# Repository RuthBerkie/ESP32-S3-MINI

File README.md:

# ESP32_S3_MINI

The Complete End-to-End System Rationale

This is a comprehensive, sequential summary of how all 6 functional blocks connect, interact, and operate dynamically as a unified system. It is structured in the exact order that electricity and data flow through the board—from the moment the plug is plugged in a cable to the execution of software tasks.
 
                       [1. USB-C Input & ESD] ───> [2. Power Conditioning (LDO)] ───> [3. 3.3V System Rails Active]
                                                                                                 │
                          ┌──────────────────────────────────────────────────────────────────────┘
                          │
                          ▼
                      [4. ESP32-S3 Boot up Sequence] <─── [RC Delay Network (10ms Lock)]
                          │
                          ├───> [5. Environmental Telemetry Bus] ───> Reading Onboard HDC3022 Sensor & Qwiic Port
                          │
                          ├───> [6. Peripheral Interaction Arrays] ──> Driving Common-Anode RGB LED Matrix
                          │
                          └───> [7. High-Speed External Expansion] ──> Driving Industrial 10-Pin SPI/IRQ Interface

Step 1: Power Entry, Handshaking, and Frontline Protection 
The entire operational sequence begins at J1 (the USB-C port).

    1. The Power Handshake: When a modern USB-C to USB-C cable is used, the host charger inspects the configuration channel pins (CC1/CC2). Because the 5.1 kΩ pull-down resistors is placed (R7/R8) on these lines, the charger identifies the board as a safe power sink and turns on its 5V rail.
    2. First Line of Defense (ESD): As the user inserts the cable, any invisible static electricity shock from their fingers is instantly intercepted by U3 (the USBLC6-2SC6 TVS diode array), which clamps the high voltage and dumps it safely to the ground plane before it can enter the rest of the board.
    3. Overcurrent Intercept: The raw 5V power travels through F1 (the 1A Polyfuse). If a downstream component is shorted, this fuse heats up and chokes the current to protect your computer's USB port.
    4. Noise Choking: The electricity then passes through FB1 (the Ferrite Bead), which blocks high-frequency electronic ripple from the laptop's power adapter, providing clean, smooth 5V power to the next stage.
    5. Reverse Voltage Isolation: Finally, D3 (the Schottky Diode) acts as a one-way check valve, letting this clean 5V travel onward but preventing any external programmer power from leaking backward into your computer.

Step 2: Power Conditioning and Voltage Regulation(Picture 5) 
The filtered 5V power now reaches U1 (the LM1117-3.3 Linear Regulator).

    1. Bulk Smoothing: C1 (10µF) acts as an entry reservoir, absorbing any sudden voltage shifts right at the door of the regulator.
    2. Down-Step Regulation: U1 takes the 5V and steps it down to a stable +3.3V, burning off the extra 1.7V as heat. This 3.3V line is the primary power source for all computer chips on the board.
    3. Transient Buffering: C2 (10µF) acts as an output reservoir. When downstream chips suddenly pull large currents, C2 dumps its energy into the rail instantly to keep the voltage from dropping.
    4. Visual Diagnostics: The moment the 3.3V rail stabilizes, current travels through R6 to light up D2 (the Green LED), providing a visual confirmation that the board's power system is operating correctly.

Step 3: Hardware Boot, Clock Timing, and Brain Management
With 3.3V spreading across the inner power planes of the board, the U4 (ESP32-S3-MINI-1) module wakes up.

    1. The Startup Delay: To prevent the ESP32 from turning on during mid-voltage fluctuations, R9 (10kΩ) and C5 (1µF) form an RC delay network. They force the EN (Reset) pin to stay low for exactly 10 milliseconds, holding the processor core in a reset state until the 3.3V rail is entirely stable.
    2. Boot Mode Selection: As the 10ms timer expires and the EN pin pulls high, the ESP32 looks at its configuration "strapping pins":
	• Normal Operation: If SW3 (BOOT button) is sitting idle, GPIO0 is pulled high internally, and the chip boots straight into its flash memory to run your saved code.
	• Flashing Mode: If you hold SW3 down while tapping SW2 (RESET), GPIO0 drops to 0V (Ground). The chip detects this and switches into its download mode, allowing a computer connected via the J4 Programming Header to upload a new script over the ESP_TXD and ESP_RXD serial lines.
    3. Noise Stability: Local 10µF (C6) and 100nF (C7) decoupling capacitors sit right at the ESP32's power pins, acting as high-frequency filters to absorb voltage fluctuations caused by the processor's internal transistors.
    4. Boot Rule Adherence: R11 (the external 10kΩ pull-up) keeps GPIO3 locked safely at 3.3V, satisfying the Espressif datasheet note to prevent a floating state from causing unpredictable boot failures.

Step 4: Environmental Data Collection via the Telemetry Bus (Picture 7)
Once the ESP32-S3 code begins running, it initializes its internal I2C communication peripheral mapped to pins 12 and 13.

    1. Line Stabilization: R1 (4.7kΩ) and R2 (4.7kΩ) act as active pull-ups, holding the SDA (Serial Data) and SCL (Serial Clock) lines at 3.3V so they don't drift into electrical noise.
    2. Onboard Telemetry: The ESP32 acts as the master, pulsing the SCL line to establish a clock rhythm. It addresses U2 (the HDC3022 sensor) using its hardwired I2C address (0x44, established by grounding its address selection pins). The sensor reads local relative humidity and temperature, sending the digital results back along the SDA line. C4 (100nF) ensures that high-precision analog measurements inside U2 are shielded from digital board noise.
    3. Modular Expansion: Simultaneously, this exact same I2C bus routes out to J2 (the Qwiic connector), allowing you to daisy-chain external sensors into the exact same communication pipeline without soldering.

Step 5: User Feedback and Industrial Peripherals (Pictures 5 & 6)
With environmental data safely inside the processor, the ESP32 executes its final tasks: outputting information to the user and interacting with external hardware expansion modules.

    1. Visual Reporting (Picture 6): Based on the data received from the sensor, the ESP32 manages the status display using D1 (the Common-Anode RGB LED). Because the anode is tied directly to 3.3V, the ESP32 uses active-low logic: it pulls LED_R, LED_G, or LED_B down to Ground to complete the circuit. The 1kΩ series resistors (R3–R5) limit the current to prevent the LED from burning out. For example, if the temperature is safe, it pulls LED_G low to flash a green status light; if a sensor error occurs, it pulls LED_R low to turn on a red warning light.
    2. User Input Handling (Picture 5): The processor constantly monitors SW1 (the USER button) via the USER_SW trace. When a user physically presses the button, the trace drops to 0V. D4 (a TVS diode) protects the delicate microcontroller pin from any static electricity generated by the user's touch. The software reads this input change and can execute custom actions, such as changing the display color or cycling modes.
    3. High-Speed Industrial Output (Picture 6): For advanced hardware configurations, the ESP32 communicates with high-density components (like an external display or an SD storage array) broken out on J3 (the 10-pin expansion header). It pushes high-speed data synchronously over the MOSI, MISO, and CLK lines, controls device activation via CS, resets external modules via the RESET pin, and catches real-world hardware alerts instantly via the dedicated IRQ (Interrupt Request) input pin.

The 4-Layer PCB Stackup

    LAYER 1: Top(F.Cu) ── Components, High-Speed Signals, RF Antenna Feed
                   - Thin prepreg isolation dielectric layer
    LAYER 2: Inner 1   ── Continuous Ground (GND) Plane (RF Return Path)
                   - Thick core material substrate
    LAYER 3: Inner 2   ── Dedicated Power (+3.3V) Plane (Low Inductance Distribution)
                   - Thin prepreg isolation dielectric layer
    LAYER 4: Bottom(B.Cu)  ── Auxiliary Signals, Mechanical Fills, Thermal GND Shielding

What is Done on Each Layer of Your Design

Layer 1: The Top Layer (F.Cu - Signal & Components)

    • What is on it: All the active components (ESP32-S3 module, HDC3022 sensor, LDO, switches,and LEDs), component solder pads, and high-speed data interconnects.
    • Its Engineering Role: It contains the most critical, high-speed traces (such as the D+/D- USB line pair and the SDA/SCL I2C lines). Keeping these lines on the top layer eliminates the need to push them through vias, lowering parasitic capacitance and minimizing data transmission errors.

Layer 2: Inner Layer 1 (In1.Cu - Continuous Ground Plane)

    • What is on it: A solid, continuous sheet of copper completely poured and dedicated to GND (Zero-Volt reference).
    • Its Engineering Role: This layer acts as a mirror directly underneath the Top Layer. Every electrical pulse traveling through a top trace creates a perfectly paired return current flowing through this ground plane. By leaving this inner plane completely unbroken, you eliminate electrical loops, dramatically lower board-level noise, and create a solid shielding floor for the 2.4GHz Wi-Fi antenna feed.

Layer 3: Inner Layer 2 (In2.Cu - Dedicated Power Plane)

    • What is on it: A solid copper plane completely poured and dedicated to the regulated +3.3V system power rail.
    • Its Engineering Role: When the ESP32 activates its Wi-Fi transmitter, it demands sharp bursts of current. Instead of choking that power through narrow, restrictive traces, the solid power plane distributes voltage like a massive highway, reducing voltage drops. Additionally, because the solid +3.3V plane sits directly parallel to the solid GND plane on Layer 2, they act as a massive structural capacitor, filtering out high-frequency switching noise automatically before it can distort your telemetry data.

Layer 4: The Bottom Layer (B.Cu - Auxiliary Routing & Thermal Shielding)

    • What is on it: Low-speed control lines (such as the manual switch routes), extra grounding fills, and the through-hole mechanical mounting pins of connectors like the USB-C port (J1).
    • Its Engineering Role: It acts as a safety valve for routing low-priority tracks that would otherwise clutter your top layer. The remaining empty space on this layer is filled with a secondary copper plane tied directly to Ground using a matrix of stitching vias. This layout configuration shields the inner signals from external radio frequency interference and draws thermal energy away from the linear regulator (U1) and the ESP32 processing core, letting the PCB act as a physical heat sink.

CONNECTIONS

1. Power & Core Ground Connections

       • Pin 3 (3V3): Connects directly to the inner +3.3V power plane (In2.Cu). This plane distributes power to the local decoupling capacitors (C6, C7), the LDO output (U1), the pull-up resistors (R1, R2, R9, R10, R11), the HDC3022 sensor (U2), the Qwiic port (J2), the RGB LED anode (D1), and the I/O expansions (J3, J4).
       • Pins 1, 45, and Center Thermal Pad (GND): Tie directly into the solid inner Ground plane (In1.Cu) through multiple stitching vias. This provides the 0V reference for every bypass capacitor, protection diode, and switch on the board.

2. Environmental Sensors & Modular Expansion (I2C Bus)

       • Pin 12 (GPIO8 / SDA) & Pin 13 (GPIO9 / SCL): These two pins form the shared I2C telemetry bus.
	   • They route horizontally to the right across the board to the HDC3022 Sensor (U2) (Pin 1 for SDA, Pin 4 for SCL).
	   • They continue to the right edge to hook into the Qwiic Connector (J2) (Pin 3 for SDA, Pin 4 for SCL).
	   • They are vertically pulled up to the 3.3V rail nearby via the 4.7kΩ resistors (R1, R2).

3. High-Speed System Expansion Header (J3 SPI Bus)

The left column of pins on the MCU module breaks out vertically to the 10-pin I/O expansion header (J3) on the left edge of the board:

    • Pin 14 (GPIO10 / CS): Routes directly to J3 Pin 4 (Chip Select control).
    • Pin 15 (GPIO11 / MOSI): Routes directly to J3 Pin 5 (Data Output line).
    • Pin 16 (GPIO12 / CLK): Routes directly to J3 Pin 6 (Serial Clock line).
    • Pin 17 (GPIO13 / MISO): Routes directly to J3 Pin 7 (Data Input line).
    • Pin 18 (GPIO14 / RESET): Routes to J3 Pin 3 to allow external device resetting.
    • Pin 19 (GPIO15 / IRQ): Routes to J3 Pin 8 for external hardware interrupt signaling.

4. Direct USB Data Interface (USB-C Programming)

       • Pin 23 (GPIO19 / USB_D-) & Pin 24 (GPIO20 / USB_D+): These high-speed differential lines route straight down the center of the board.
         	• They pass cleanly through the channels of the U3 ESD protection chip (USBLC6-2SC6).
         	• They land directly onto pins A7/B7 (D-) and A6/B6 (D+) of the USB-C port (J1) for native computer communication.

5. Status Diagnostics (RGB LED Matrix)

The right-hand GPIO block routes down towards the bottom right corner to drive the status indicator:

    • Pin 35 (GPIO38 / LED_R): Routes down to the current-limiting resistor R3, landing on D1 Pin 2 (Red Channel).
    • Pin 36 (GPIO39 / LED_G): Routes down to the current-limiting resistor R4, landing on D1 Pin 3 (Green Channel).
    • Pin 37 (GPIO40 / LED_B): Routes down to the current-limiting resistor R5, landing on D1 Pin 4 (Blue Channel).

6. Physical User UI Switches & Legacy Programming

       • Pin 27 (GPIO47 / USER_SW): Routes along the lower right-hand edge to the SW1 user switch circuit, protected by the D4 TVS diode.
       • Pin 45 (EN / Chip Reset): Routes to the RESET button (SW2), the R9/C5 10ms delay network, the D5 TVS diode, and Pin 1 of the J4 programming dock.
       • Pin 4 (GPIO0 / BOOT): Routes straight to the BOOT button (SW3), the R10/C8 debounce network, the D6 TVS diode, and Pin 6 of the J4 programming dock.
       • Pin 39 (GPIO43 / TXD) & Pin 40 (GPIO44 / RXD): These traditional UART serial lines route directly across to the 6-pin programming header (J4) (Pin 3 for TXD, Pin 5 for RXD) for automated lab debugging equipment.

   FINAL RESULT

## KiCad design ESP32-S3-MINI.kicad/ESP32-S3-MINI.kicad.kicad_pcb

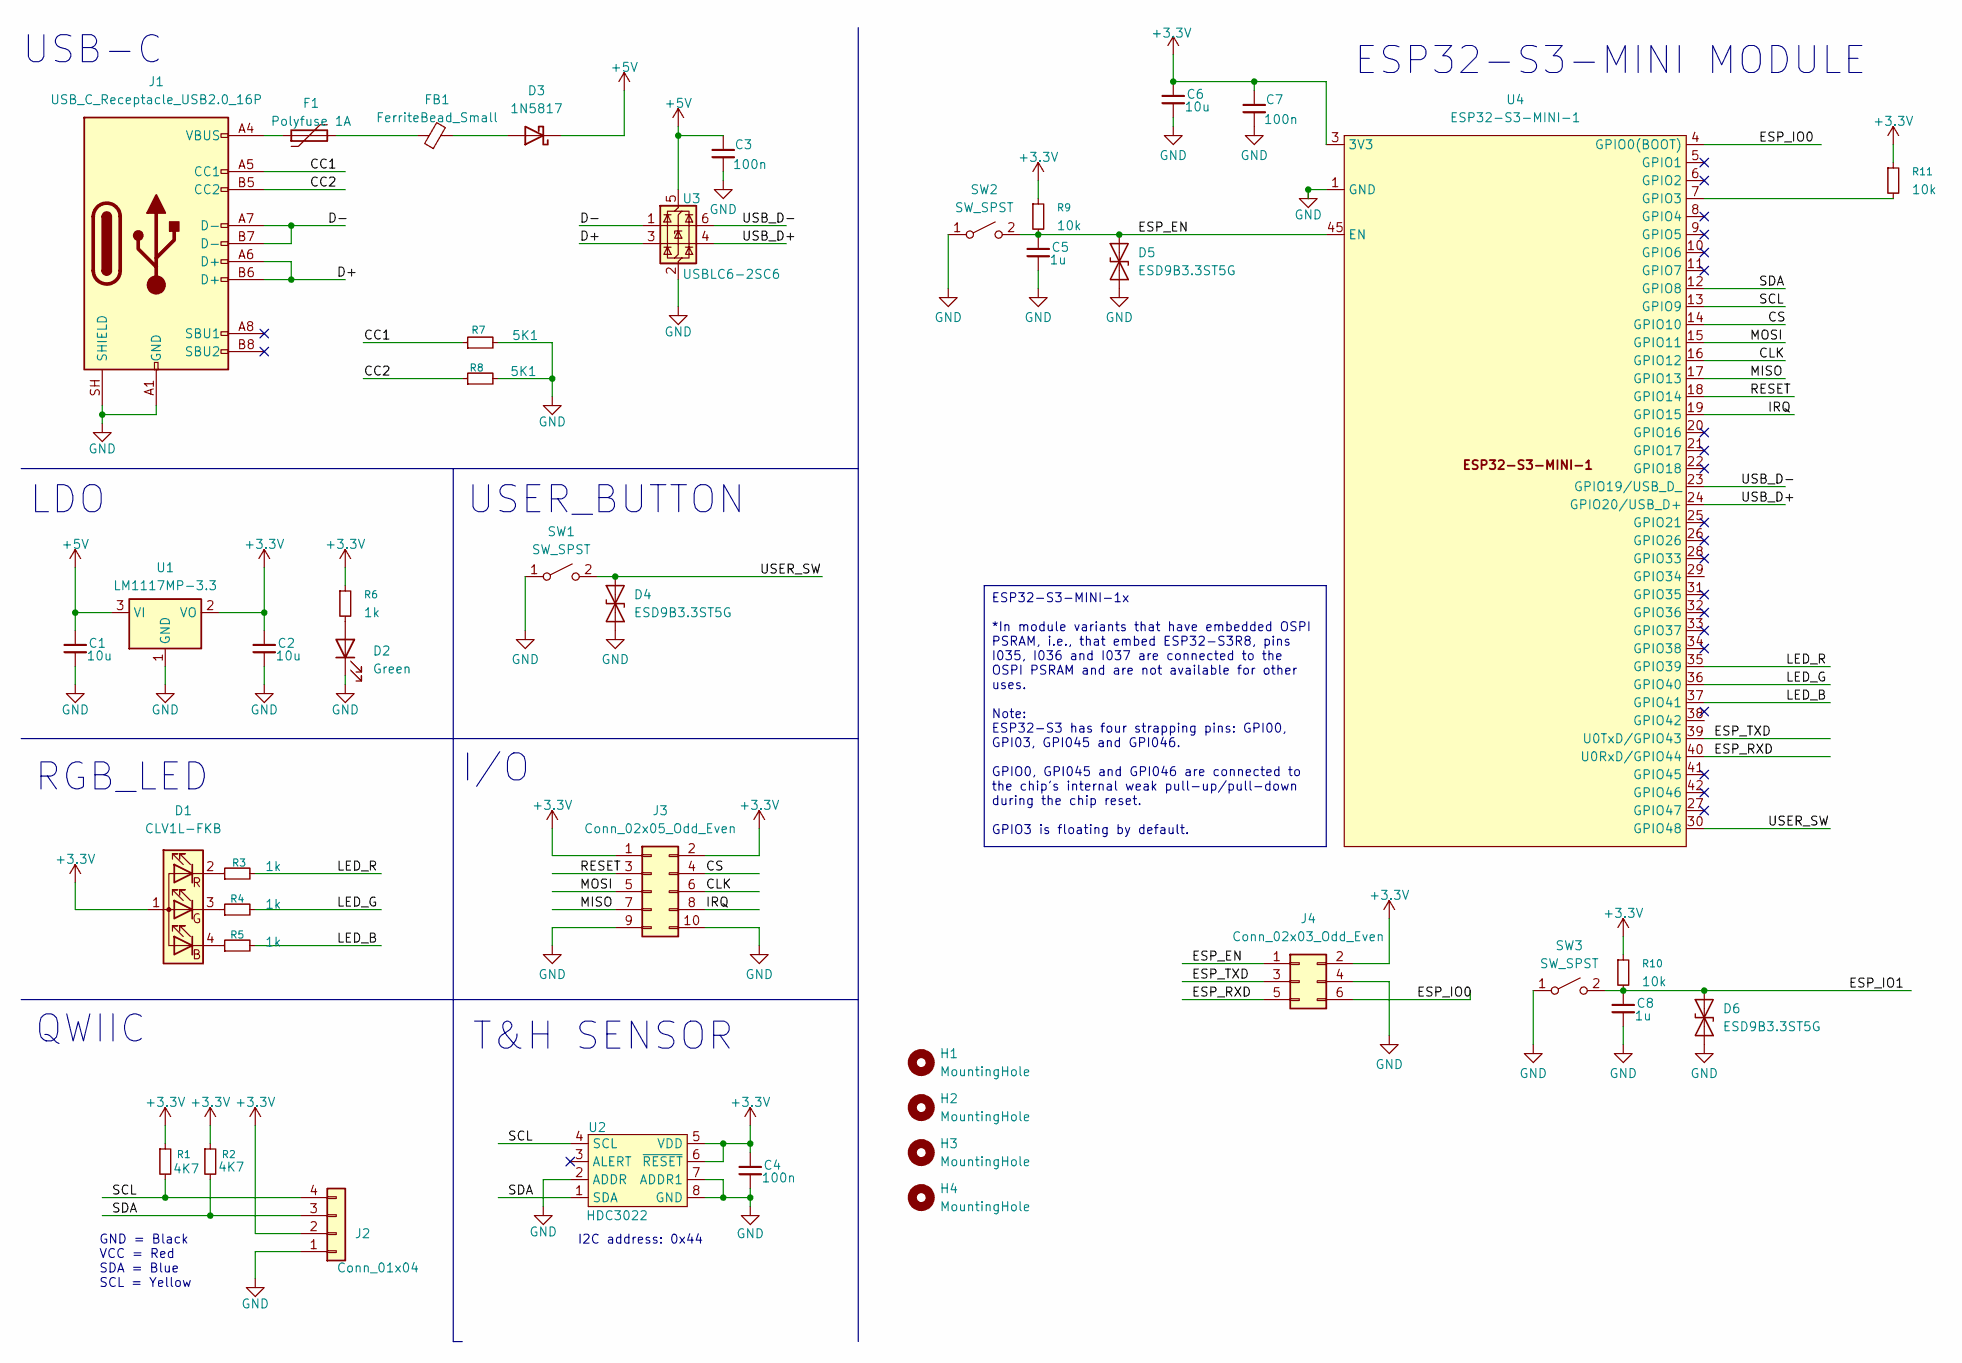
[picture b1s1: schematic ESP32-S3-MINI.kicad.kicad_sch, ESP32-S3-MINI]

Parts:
C1, C2, C6: 10u; C_0603_1608Metric
C3, C4, C7: 100n; C_0402_1005Metric
C5, C8: 1u; C_0603_1608Metric
D1: CLV1L-FKB; LED_Cree-PLCC4_3.2x2.8mm_CCW
D2: Green; LED_0603_1608Metric
D3: 1N5817; D_DO-41_SOD81_P10.16mm_Horizontal
D4, D5, D6: ESD9B3.3ST5G; D_SOD-923
F1: Polyfuse 1A; Fuse_1206_3216Metric
FB1: FerriteBead_Small; LED_0805_2012Metric_Pad1.15x1.40mm_HandSolder
H1, H2, H3, H4: MountingHole; MountingHole_3.2mm_M3_DIN965
J1: USB_C_Receptacle_USB2.0_16P; USB_C_Receptacle_HRO_TYPE-C-31-M-12
J2: Conn_01x04; JST_SH_SM04B-SRSS-TB_1x04-1MP_P1.00mm_Horizontal
J3: Conn_02x05_Odd_Even; PinHeader_2x05_P2.54mm_Vertical
J4: Conn_02x03_Odd_Even; PinHeader_2x03_P2.54mm_Vertical
R1, R2: 4K7; R_0402_1005Metric
R3, R4, R5, R6: 1k; R_0402_1005Metric
R7, R8: 5K1; R_0402_1005Metric
R9, R10, R11: 10k; R_0402_1005Metric
SW1: SW_SPST; SW_Tactile_SPST_Angled_PTS645Vx31-2LFS
SW2, SW3: SW_SPST; SW_SPST_B3U-1000P
U1: LM1117MP-3.3; SOT-223-3_TabPin2
U2: HDC3022; DEJ0008A-C01-IPC_A
U3: USBLC6-2SC6; SOT-23-6
U4: ESP32-S3-MINI-1

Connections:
+3.3V: C2.1, C4.1, C6.1, C7.1, D1.1 (A), J2.2, J3.1, J3.2, J4.2, R1.1, R2.1, R6.1, R9.1, R10.1, R11.1, U1.2 (VO), U2.5 (VDD), U2.6 (~RESET), U4.3 (3V3)
+5V: C1.1, C3.1, D3.1 (K), U1.3 (VI), U3.5 (VBUS)
/CC1: J1.A5 (CC1), R7.1
/CC2: J1.B5 (CC2), R8.1
/CLK: J3.6, U4.16 (GPIO12)
/CS: J3.4, U4.14 (GPIO10)
/D+: J1.A6 (D+), J1.B6 (D+), U3.3 (I/O2)
/D-: J1.A7 (D-), J1.B7 (D-), U3.1 (I/O1)
/ESP_EN: C5.1, D5.2 (A2), J4.1, R9.2, SW2.2 (B), U4.45 (EN); also elsewhere on the board
/ESP_IO0: J4.6, U4.4 (GPIO0(BOOT))
/ESP_IO1: C8.1, D6.2 (A2), R10.2, SW3.2 (B); also elsewhere on the board
/ESP_RXD: J4.5, U4.40 (U0RxD/GPIO44)
/ESP_TXD: J4.3, U4.39 (U0TxD/GPIO43)
/IRQ: J3.8, U4.19 (GPIO15)
/LED_B: R5.2, U4.37 (GPIO41)
/LED_G: R4.2, U4.36 (GPIO40)
/LED_R: R3.2, U4.35 (GPIO39)
/MISO: J3.7, U4.17 (GPIO13)
/MOSI: J3.5, U4.15 (GPIO11)
/RESET: J3.3, U4.18 (GPIO14)
/SCL: J2.4, R1.2, U2.4 (SCL), U4.13 (GPIO9)
/SDA: J2.3, R2.2, U2.1 (SDA), U4.12 (GPIO8)
/USB_D+: U3.4 (I/O2), U4.24 (GPIO20/USB_D+)
/USB_D-: U3.6 (I/O1), U4.23 (GPIO19/USB_D_)
/USER_SW: D4.2 (A2), SW1.2 (B), U4.30 (GPIO48)
GND: C1.2, C2.2, C3.2, C4.2, C5.2, C6.2, C7.2, C8.2, D2.1 (K), D4.1 (A1), D5.1 (A1), D6.1 (A1), J1.A1 (GND), J1.A12 (GND), J1.B1 (GND), J1.B12 (GND), J1.SH (SHIELD), J2.1, J3.9, J3.10, J4.4, R7.2, R8.2, SW1.1 (A), SW2.1 (A), SW3.1 (A), U1.1 (GND), U2.2 (ADDR), U2.7 (ADDR1), U2.8 (GND), U3.2 (GND), U4.1 (GND); also elsewhere on the board
unnamed: D1.4 (BK), R5.1
unnamed: D1.3 (GK), R4.1
unnamed: D1.2 (RK), R3.1
unnamed: D2.2 (A), R6.2
unnamed: D3.2 (A), FB1.2
unnamed: F1.1, J1.A4 (VBUS), J1.A9 (VBUS), J1.B4 (VBUS), J1.B9 (VBUS)
unnamed: F1.2, FB1.1
unnamed: R11.2, U4.7 (GPIO3)

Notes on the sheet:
RGB_LED
USB-C
ESP32-S3-MINI MODULE
QWIIC
USER_BUTTON
T&H SENSOR
LDO
I2C address: 0x44
I/O
GND = Black VCC = Red SDA = Blue SCL = Yellow
ESP32-S3-MINI-1x *In module variants that have embedded OSPI PSRAM, i.e., that embed ESP32-S3R8, pins I035, I036 and I037 are connected to the OSPI PSRAM and are not available for other uses. Note: ESP32-S3 has four strapping pins: GPI00, GPI03, GPI045 and GPI046. GPIO0, GPI045 and GPI046 are conne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

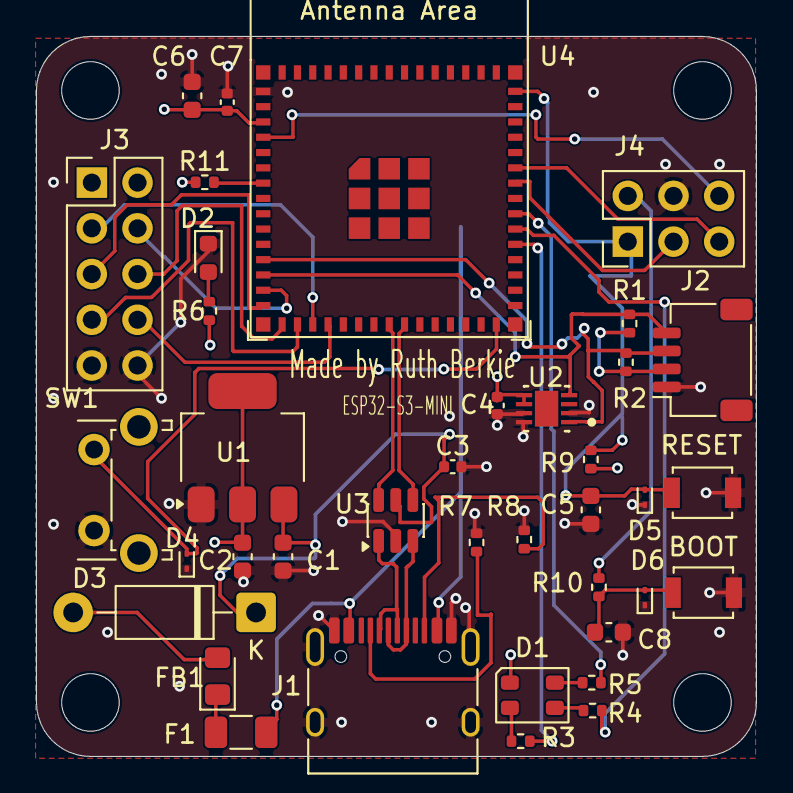
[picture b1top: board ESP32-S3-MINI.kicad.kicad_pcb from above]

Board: 4 copper layers, 40.0 x 40.0 mm, 42 parts (0 on the bottom side), 34 nets.

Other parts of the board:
BOOT: SW_SPST; SW_SPST_B3U-1000P
RESET: SW_SPST; SW_SPST_B3U-1000P

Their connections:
/ESP_EN: RESET.2 (B); also elsewhere on the board
/ESP_IO1: BOOT.2 (B); also elsewhere on the board
GND: BOOT.1 (A), RESET.1 (A); also elsewhere on the board
